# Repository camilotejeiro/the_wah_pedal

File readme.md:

The Wah Pedal
=============

Circuit implementing a simple active variable filter 
with a couple of transistors and no variable 
reactive components.

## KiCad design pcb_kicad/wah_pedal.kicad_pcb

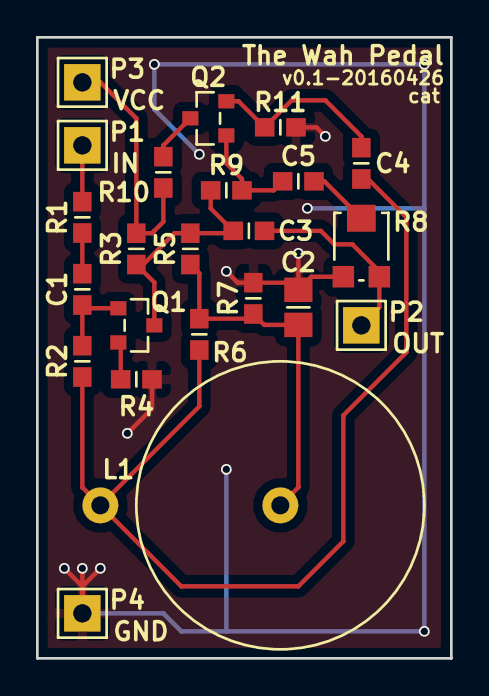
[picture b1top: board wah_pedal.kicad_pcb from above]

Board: 2 copper layers, 23.0 x 34.5 mm, 23 parts (0 on the bottom side), 14 nets.

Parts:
C1, C4: 0.01uF; 1608M-0603I-Most
C2: 4.7uF; 2012M-0805I-Most
C3, C5: 0.22uF; 1608M-0603I-Most
L1: 500mH; Vertical-TH-D16MM-H22.35MM_70F501AF-RC
P1, P2, P3, P4: CONN_01X01; 01X02-0.1IN-Straight-TH
Q1, Q2: Q-NPN-BEC; SOT-23_BC817-40LT3G
R1: 68kR; 1608M-0603I-Most
R2: 1.5kR; 1608M-0603I-Most
R3: 22kR; 1608M-0603I-Most
R4: 470R; 1608M-0603I-Most
R5, R9: 470kR; 1608M-0603I-Most
R6: 33kR; 1608M-0603I-Most
R7: 82kR; 1608M-0603I-Most
R8: 100kR; 3MM-SMD-TRIMPOT_TC33X-2-501E
R10: 1kR; 1608M-0603I-Most
R11: 10kR; 1608M-0603I-Most

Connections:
/Input: P1.1, R1.1
/Output: C3.1, P2.1, R8.3
GND: C2.2, P4.1, R4.1, R7.1, R8.1, R11.1
unnamed: C1.1, Q1.1, R2.2
unnamed: C1.2, R1.2
unnamed: C2.1, L1.1, R5.1, R6.2, R7.2
unnamed: C3.2, Q1.3, R3.1, R5.2, R9.1
unnamed: C4.1, Q2.2, R11.2
unnamed: C4.2, L1.2, R2.1, R6.1
unnamed: C5.1, Q2.1, R9.2
unnamed: C5.2, R8.2
unnamed: Q1.2, R4.2
unnamed: Q2.3, R10.1
VCC: P3.1, R3.2, R10.2

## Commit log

2016-05-03 posting the wah pedal example project
2016-05-03 adding a readme
2016-05-03 removing upperCase
2017-02-07 removed .bak
2017-07-31 changing filepaths
2017-08-28 changing sch based on new libraries, for testing
